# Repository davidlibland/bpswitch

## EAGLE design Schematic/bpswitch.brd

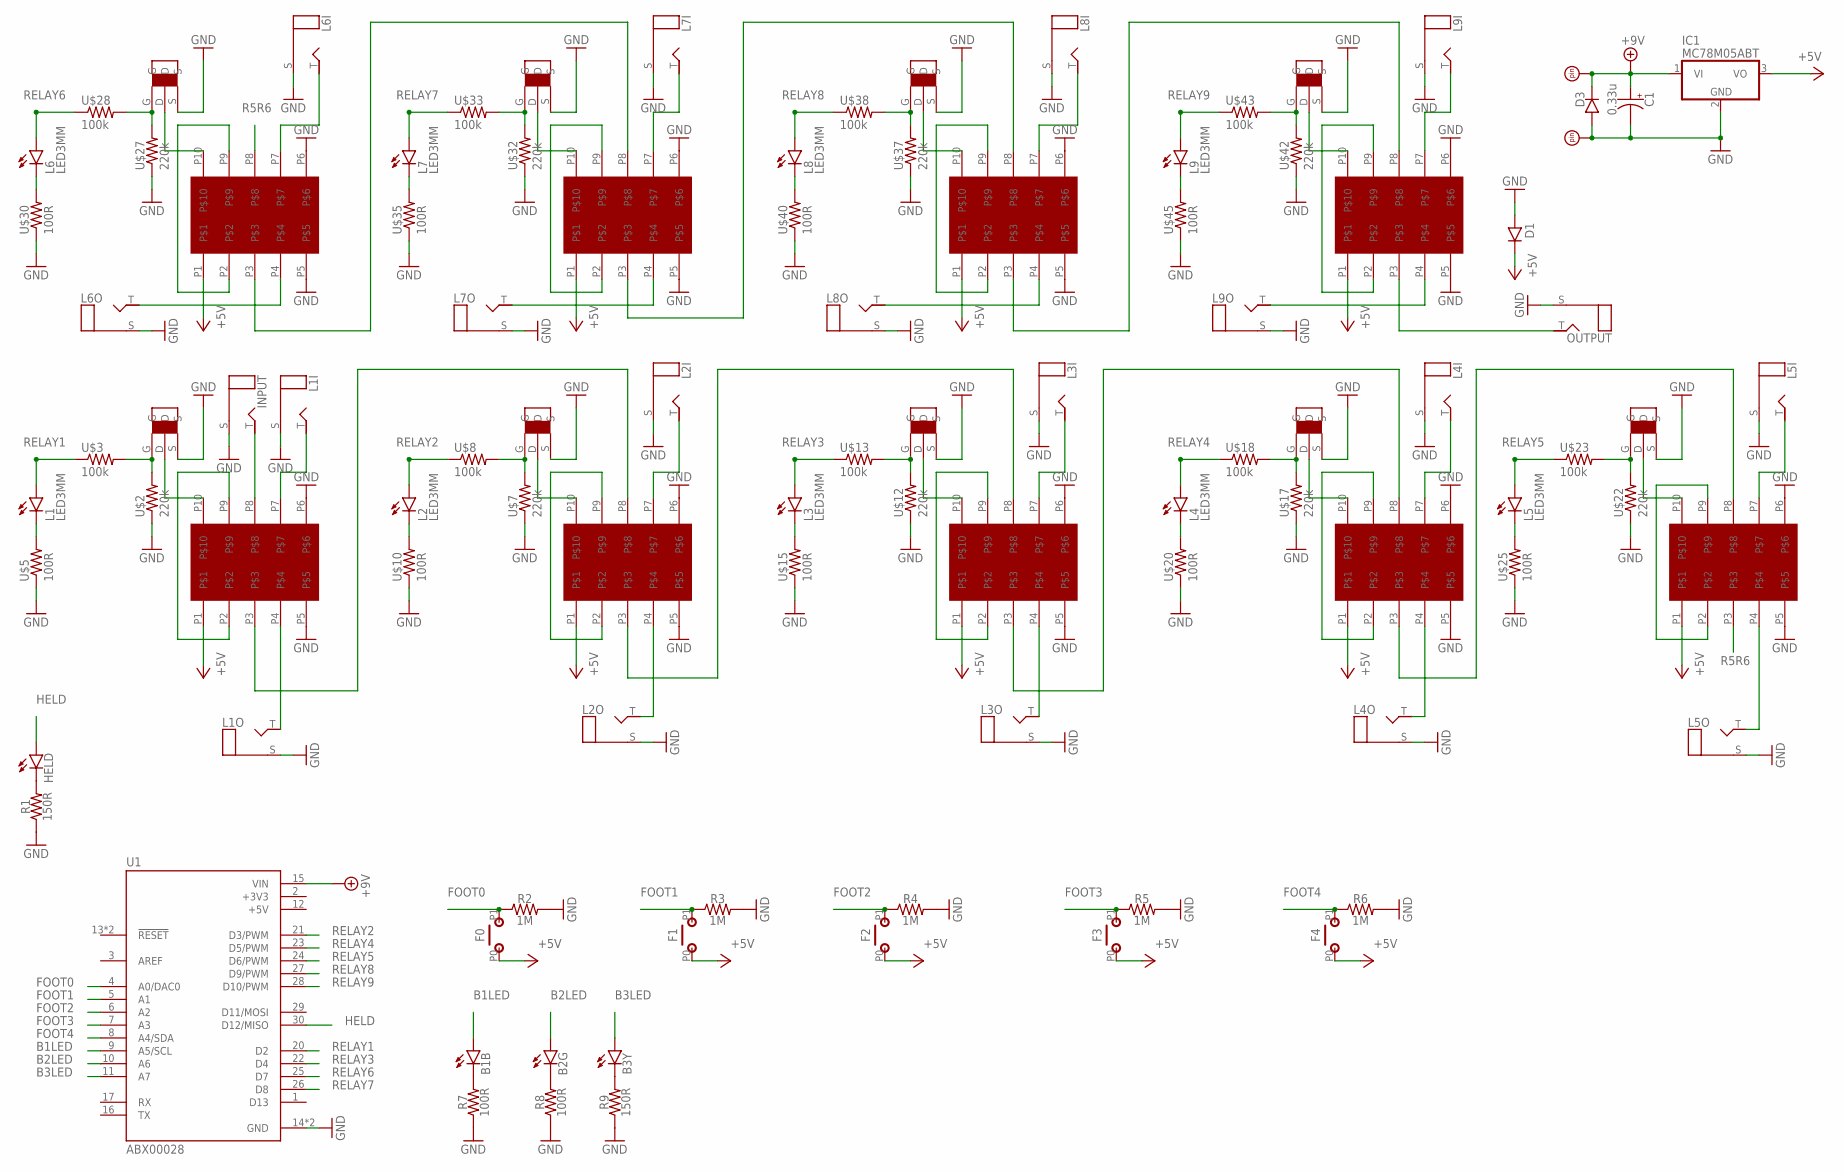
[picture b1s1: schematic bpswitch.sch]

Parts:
B1B, B2G, B3Y: LED.3; 3MM_2
C1: 0.33u; 050.FLAT
D1: 1N400X.3; DO41-3
D3: DO41.2; DO41-2
F0, F1, F2, F3, F4: MOM
HELD: LED.3; 3MM_2
IC1: MC78M05ABT; TO220V
INPUT: MONO_PADS; 2PADS
L1, L2, L3, L4, L5, L6, L7, L8, L9: LED3MM
L1I, L1O, L2I, L2O, L3I, L3O, L4I, L4O, L5I, L5O, L6I, L6O, L7I, L7O, L8I, L8O, L9I, L9O: MONO_PADS; 2PADS
OUTPUT: MONO_PADS; 2PADS
R1, R9: 150R; 0.2"
R2, R3, R4, R5, R6: 1M; 0.2"
R7, R8: 100R; 0.2"
U1: ABX00028; MODULE_ABX00028
U$1, U$6, U$11, U$16, U$21, U$26, U$31, U$36, U$41: TO-220
U$2, U$7, U$12, U$17, U$22, U$27, U$32, U$37, U$42: 220k; R0204/2
U$3, U$8, U$13, U$18, U$23, U$28, U$33, U$38, U$43: 100k; R0204/2
U$4, U$9, U$14, U$19, U$24, U$29, U$34, U$39, U$44: MINI_RELAY_10PIN
U$5, U$10, U$15, U$20, U$25, U$30, U$35, U$40, U$45: 100R; R0204/2
VI: PADS.SQR_LBL; PAD3
VO: PADS.SQR_LBL; PAD3

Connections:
+3V3: U1.2 (+3V3)
+5V: D1.C, F0.P0, F1.P0, F2.P0, F3.P0, F4.P0, IC1.3 (VO), U1.12 (+5V), U$4.P1, U$9.P1, U$14.P1, U$19.P1, U$24.P1, U$29.P1, U$34.P1, U$39.P1, U$44.P1
+9V: C1.+, D3.C, IC1.1 (VI), U1.15 (VIN), VI.1
B1LED: B1B.ANODE (A), U1.9 (A5/SCL)
B2LED: B2G.ANODE (A), U1.10 (A6)
B3LED: B3Y.ANODE (A), U1.11 (A7)
FOOT0: F0.P1 (S), R2.1, U1.4 (A0/DAC0)
FOOT1: F1.P1 (S), R3.1, U1.5 (A1)
FOOT2: F2.P1 (S), R4.1, U1.6 (A2)
FOOT3: F3.P1 (S), R5.1, U1.7 (A3)
FOOT4: F4.P1 (S), R6.1, U1.8 (A4/SDA)
GND: C1.-, D1.A, D3.A, IC1.2 (GND), INPUT.S, L1I.S, L1O.S, L2I.S, L2O.S, L3I.S, L3O.S, L4I.S, L4O.S, L5I.S, L5O.S, L6I.S, L6O.S, L7I.S, L7O.S, L8I.S, L8O.S, L9I.S, L9O.S, OUTPUT.S, R1.1, R2.2, R3.2, R4.2, R5.2, R6.2, R7.1, R8.1, R9.1, U1.14 (GND), U1.19 (GND), U$1.S, U$2.1, U$4.P5, U$4.P6, U$5.1, U$6.S, U$7.1, U$9.P5, U$9.P6, U$10.1, U$11.S, U$12.1, U$14.P5, U$14.P6, U$15.1, U$16.S, U$17.1, U$19.P5, U$19.P6, U$20.1, U$21.S, U$22.1, U$24.P5, U$24.P6, U$25.1, U$26.S, U$27.1, U$29.P5, U$29.P6, U$30.1, U$31.S, U$32.1, U$34.P5, U$34.P6, U$35.1, U$36.S, U$37.1, U$39.P5, U$39.P6, U$40.1, U$41.S, U$42.1, U$44.P5, U$44.P6, U$45.1, VO.1
HELD: HELD.ANODE (A), U1.30 (D12/MISO)
unnamed: U$1.G, U$2.2, U$3.2
unnamed: U$1.D, U$4.P10
unnamed: U$6.G, U$7.2, U$8.2
unnamed: L1.K (C), U$5.2
unnamed: U$6.D, U$9.P10
unnamed: L2.K (C), U$10.2
unnamed: U$11.G, U$12.2, U$13.2
unnamed: U$11.D, U$14.P10
unnamed: L3.K (C), U$15.2
unnamed: U$16.G, U$17.2, U$18.2
unnamed: U$16.D, U$19.P10
unnamed: L4.K (C), U$20.2
unnamed: U$21.G, U$22.2, U$23.2
unnamed: U$21.D, U$24.P10
unnamed: L5.K (C), U$25.2
unnamed: U$26.G, U$27.2, U$28.2
unnamed: U$26.D, U$29.P10
unnamed: L6.K (C), U$30.2
unnamed: U$31.G, U$32.2, U$33.2
unnamed: U$31.D, U$34.P10
unnamed: L7.K (C), U$35.2
unnamed: U$36.G, U$37.2, U$38.2
unnamed: U$36.D, U$39.P10
unnamed: L8.K (C), U$40.2
unnamed: U$41.G, U$42.2, U$43.2
unnamed: U$41.D, U$44.P10
unnamed: L9.K (C), U$45.2
unnamed: U$4.P2, U$4.P9
unnamed: U$9.P2, U$9.P9
unnamed: U$14.P2, U$14.P9
unnamed: U$19.P2, U$19.P9
unnamed: U$24.P2, U$24.P9
unnamed: U$44.P2, U$44.P9
unnamed: U$39.P2, U$39.P9
unnamed: U$34.P2, U$34.P9
unnamed: U$29.P2, U$29.P9
unnamed: U$4.P3, U$9.P8
unnamed: U$9.P3, U$14.P8
unnamed: U$14.P3, U$19.P8
unnamed: U$19.P3, U$24.P8
unnamed: U$29.P3, U$34.P8
unnamed: U$34.P3, U$39.P8
unnamed: U$39.P3, U$44.P8
unnamed: L1I.T, U$4.P7
unnamed: INPUT.T, U$4.P8
unnamed: L1O.T, U$4.P4
unnamed: L6O.T, U$29.P4
unnamed: L6I.T, U$29.P7
unnamed: L7O.T, U$34.P4
unnamed: L7I.T, U$34.P7
unnamed: L8O.T, U$39.P4
unnamed: L8I.T, U$39.P7
unnamed: L9I.T, U$44.P7
unnamed: L9O.T, U$44.P4
unnamed: OUTPUT.T, U$44.P3
unnamed: L5I.T, U$24.P7
unnamed: L5O.T, U$24.P4
unnamed: L4O.T, U$19.P4
unnamed: L3O.T, U$14.P4
unnamed: L3I.T, U$14.P7
unnamed: L2I.T, U$9.P7
unnamed: L2O.T, U$9.P4
unnamed: L4I.T, U$19.P7
unnamed: HELD.P$1 (C), R1.2
unnamed: B1B.P$1 (C), R7.2
unnamed: B2G.P$1 (C), R8.2
unnamed: B3Y.P$1 (C), R9.2
R5R6: U$24.P3, U$29.P8
RELAY1: L1.A, U1.20 (D2), U$3.1
RELAY2: L2.A, U1.21 (D3/PWM), U$8.1
RELAY3: L3.A, U1.22 (D4), U$13.1
RELAY4: L4.A, U1.23 (D5/PWM), U$18.1
RELAY5: L5.A, U1.24 (D6/PWM), U$23.1
RELAY6: L6.A, U1.25 (D7), U$28.1
RELAY7: L7.A, U1.26 (D8), U$33.1
RELAY8: L8.A, U1.27 (D9/PWM), U$38.1
RELAY9: L9.A, U1.28 (D10/PWM), U$43.1

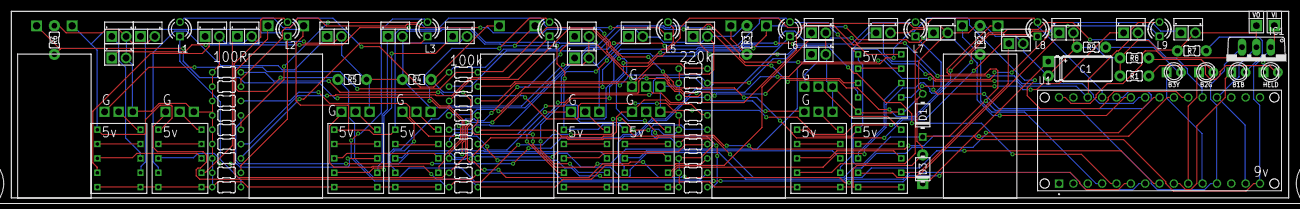
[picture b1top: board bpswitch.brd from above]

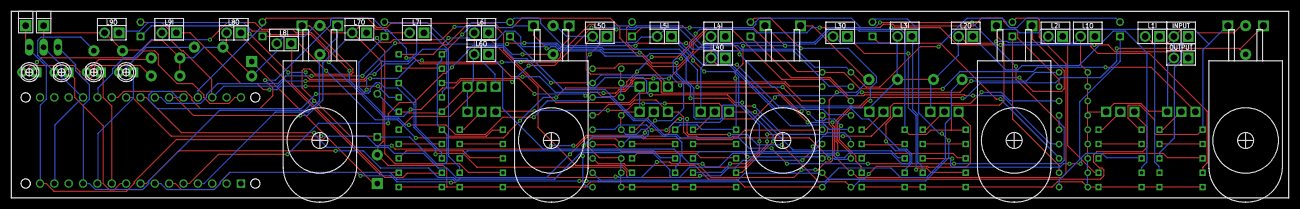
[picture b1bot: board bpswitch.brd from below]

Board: 2 copper layers, 226.1 x 33.0 mm, 116 parts (10 on the bottom side), 89 nets.

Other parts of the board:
U$46: 1032L
U$47, U$48, U$49, U$50, U$51, U$52, U$53, U$54, U$55, U$57: LUMBURG_TOP
U$56: DC_TOP
U$58, U$59, U$60, U$61, U$62: MOMENTARY

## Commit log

2021-09-15 Initial code for loop mode
2021-09-16 Added preset code
2021-09-16 Added code to load presets
2021-09-17 Simplified to single bank of presets
2021-09-17 Working code
2021-09-20 Cleaned & isolated insertLoc code
2021-09-20 Optimized generated code
2021-09-23 Added ability to save presets
2022-02-01 Inital code commit
2022-09-18 Added schematic
2023-02-24 Added updates
